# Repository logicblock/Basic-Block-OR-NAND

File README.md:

### Basic Block - 7400 Quad 2-input NAND & 7432 Quad 2-input OR

*Scale 1:1*

### Where to buy it?
Coming soon on Tindie

### Licence
**Basic Block - 7400 Quad 2-input NAND & 7432 Quad 2-input OR** are licenced under [Creative Commons Attribution and Share Alike 4.0 International](https://github.com/logicblock/Basic-Block-OR-NAND/blob/master/LICENSE.md) by [J.Rodrigo](http://www.jrodrigo.net).

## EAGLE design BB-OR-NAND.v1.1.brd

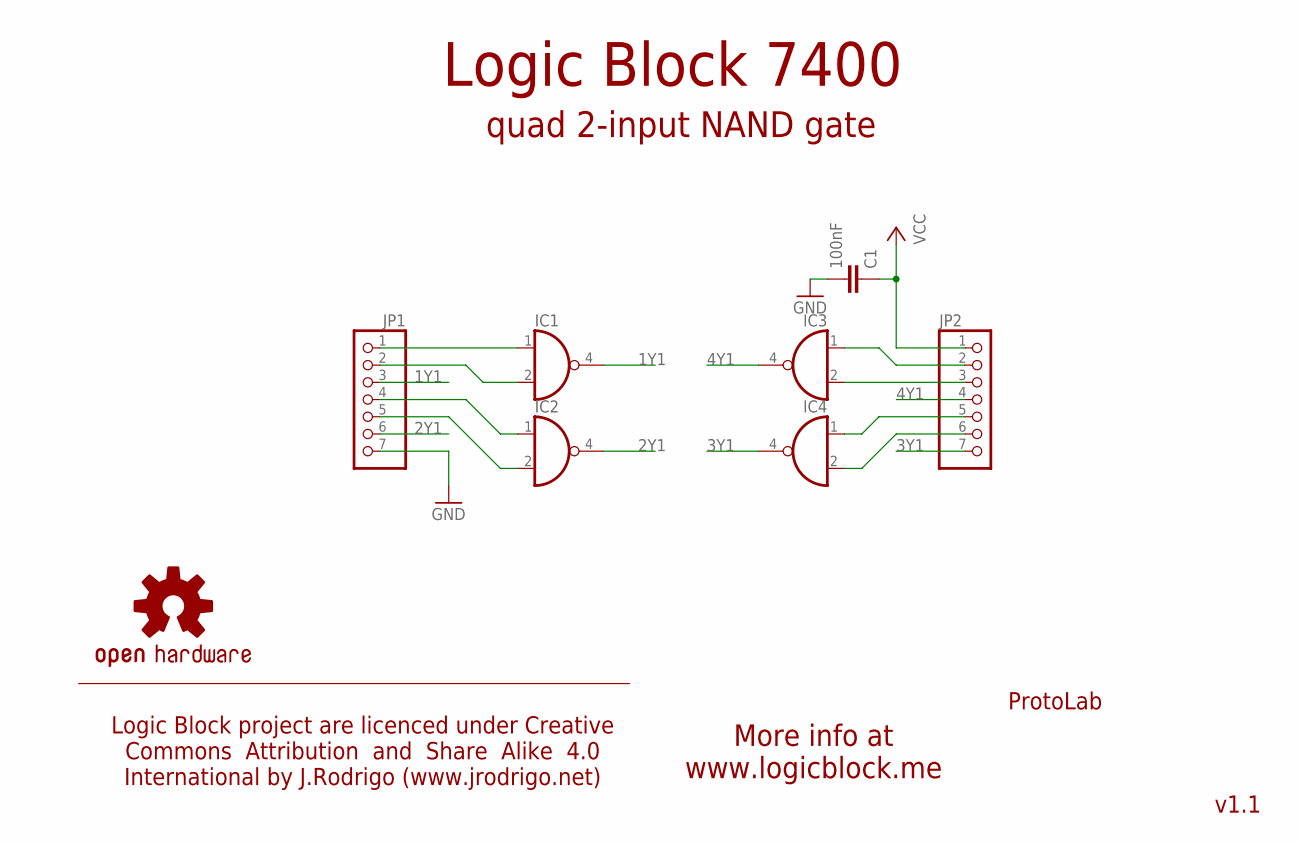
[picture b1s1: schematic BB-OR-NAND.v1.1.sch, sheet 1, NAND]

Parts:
C1: 100nF; C0603K
IC1, IC2, IC3, IC4: 74AHC1G00DCK; SC70-5
JP1, JP2: CON_1X7CLEANBIG; CON_1X07-CLEANBIG
U$1: OSHW-LOGOS-LAYER230; OSHW-LOGO-S_LAYER230

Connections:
1Y1: IC1.4 (O), JP1.3
2Y1: IC2.4 (O), JP1.6
3Y1: IC4.4 (O), JP2.7
4Y1: IC3.4 (O), JP2.4
GND: C1.2, IC1.3 (GND), IC2.3 (GND), IC3.3 (GND), IC4.3 (GND), JP1.7; also elsewhere on the board
unnamed: IC1.1 (I0), JP1.1
unnamed: IC1.2 (I1), JP1.2
unnamed: IC4.2 (I1), JP2.6
unnamed: IC2.1 (I0), JP1.4
unnamed: IC2.2 (I1), JP1.5
unnamed: IC4.1 (I0), JP2.5
unnamed: IC3.2 (I1), JP2.3
unnamed: IC3.1 (I0), JP2.2
VCC: C1.1, IC1.5 (VCC), IC2.5 (VCC), IC3.5 (VCC), IC4.5 (VCC), JP2.1; also elsewhere on the board

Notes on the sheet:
ProtoLab
v1.1
More info at www.logicblock.me
Logic Block 7400
quad 2-input NAND gate
Logic Block project are licenced under Creative Commons Attribution and Share Alike 4.0 International by J.Rodrigo (www.jrodrigo.net)

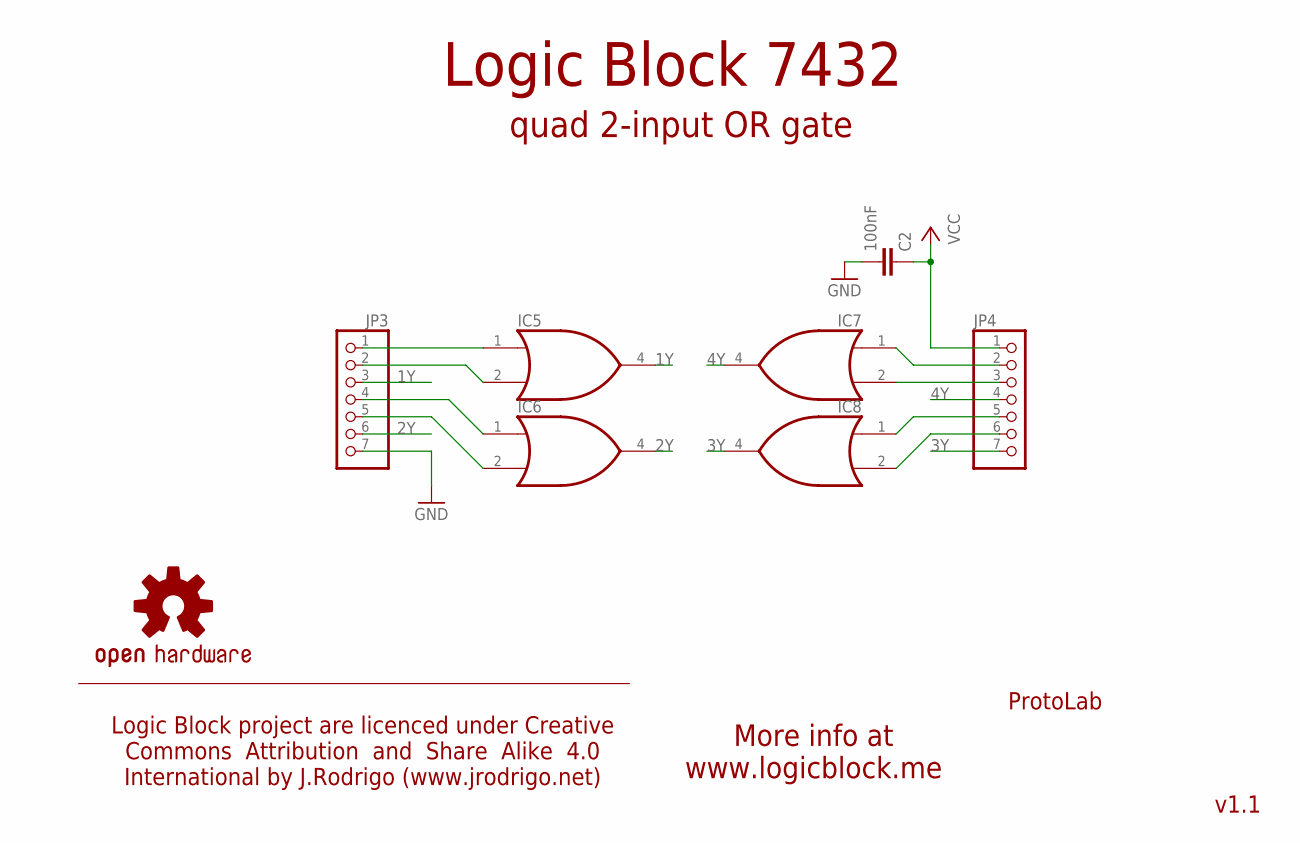
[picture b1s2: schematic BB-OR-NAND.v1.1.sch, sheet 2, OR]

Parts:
C2: 100nF; C0603K
IC5, IC6, IC7, IC8: 74AHC1G32DCK; SC70-5
JP3, JP4: CON_1X7CLEANBIG; CON_1X07-CLEANBIG
U$2: OSHW-LOGOS-LAYER230; OSHW-LOGO-S_LAYER230

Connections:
1Y: IC5.4 (O), JP3.3
2Y: IC6.4 (O), JP3.6
3Y: IC8.4 (O), JP4.7
4Y: IC7.4 (O), JP4.4
GND: C2.2, IC5.3 (GND), IC6.3 (GND), IC7.3 (GND), IC8.3 (GND), JP3.7; also elsewhere on the board
unnamed: IC5.1 (I0), JP3.1
unnamed: IC5.2 (I1), JP3.2
unnamed: IC6.1 (I0), JP3.4
unnamed: IC6.2 (I1), JP3.5
unnamed: IC8.2 (I1), JP4.6
unnamed: IC8.1 (I0), JP4.5
unnamed: IC7.2 (I1), JP4.3
unnamed: IC7.1 (I0), JP4.2
VCC: C2.1, IC5.5 (VCC), IC6.5 (VCC), IC7.5 (VCC), IC8.5 (VCC), JP4.1; also elsewhere on the board

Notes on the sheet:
ProtoLab
v1.1
More info at www.logicblock.me
Logic Block 7432
quad 2-input OR gate
Logic Block project are licenced under Creative Commons Attribution and Share Alike 4.0 International by J.Rodrigo (www.jrodrigo.net)

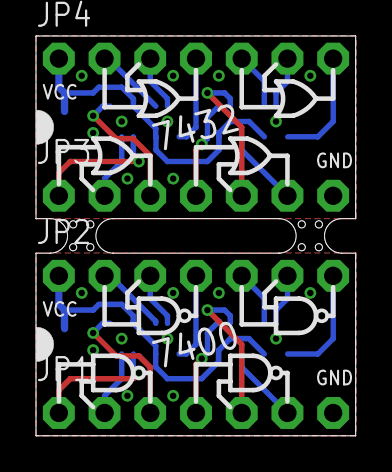
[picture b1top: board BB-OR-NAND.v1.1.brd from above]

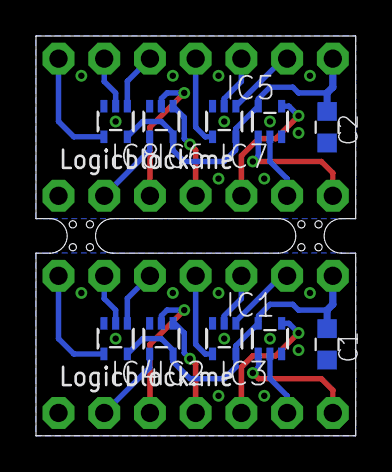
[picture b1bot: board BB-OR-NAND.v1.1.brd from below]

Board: 2 copper layers, 17.8 x 22.2 mm, 16 parts (10 on the bottom side), 26 nets.

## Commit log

2015-12-08 Created README.md
2015-12-08 added LICENSE.md
2015-12-08 Fixed links on README.md
2015-12-08 First release
    First release of board
2015-12-08 Added gerbers
    Added gerbers files from board
